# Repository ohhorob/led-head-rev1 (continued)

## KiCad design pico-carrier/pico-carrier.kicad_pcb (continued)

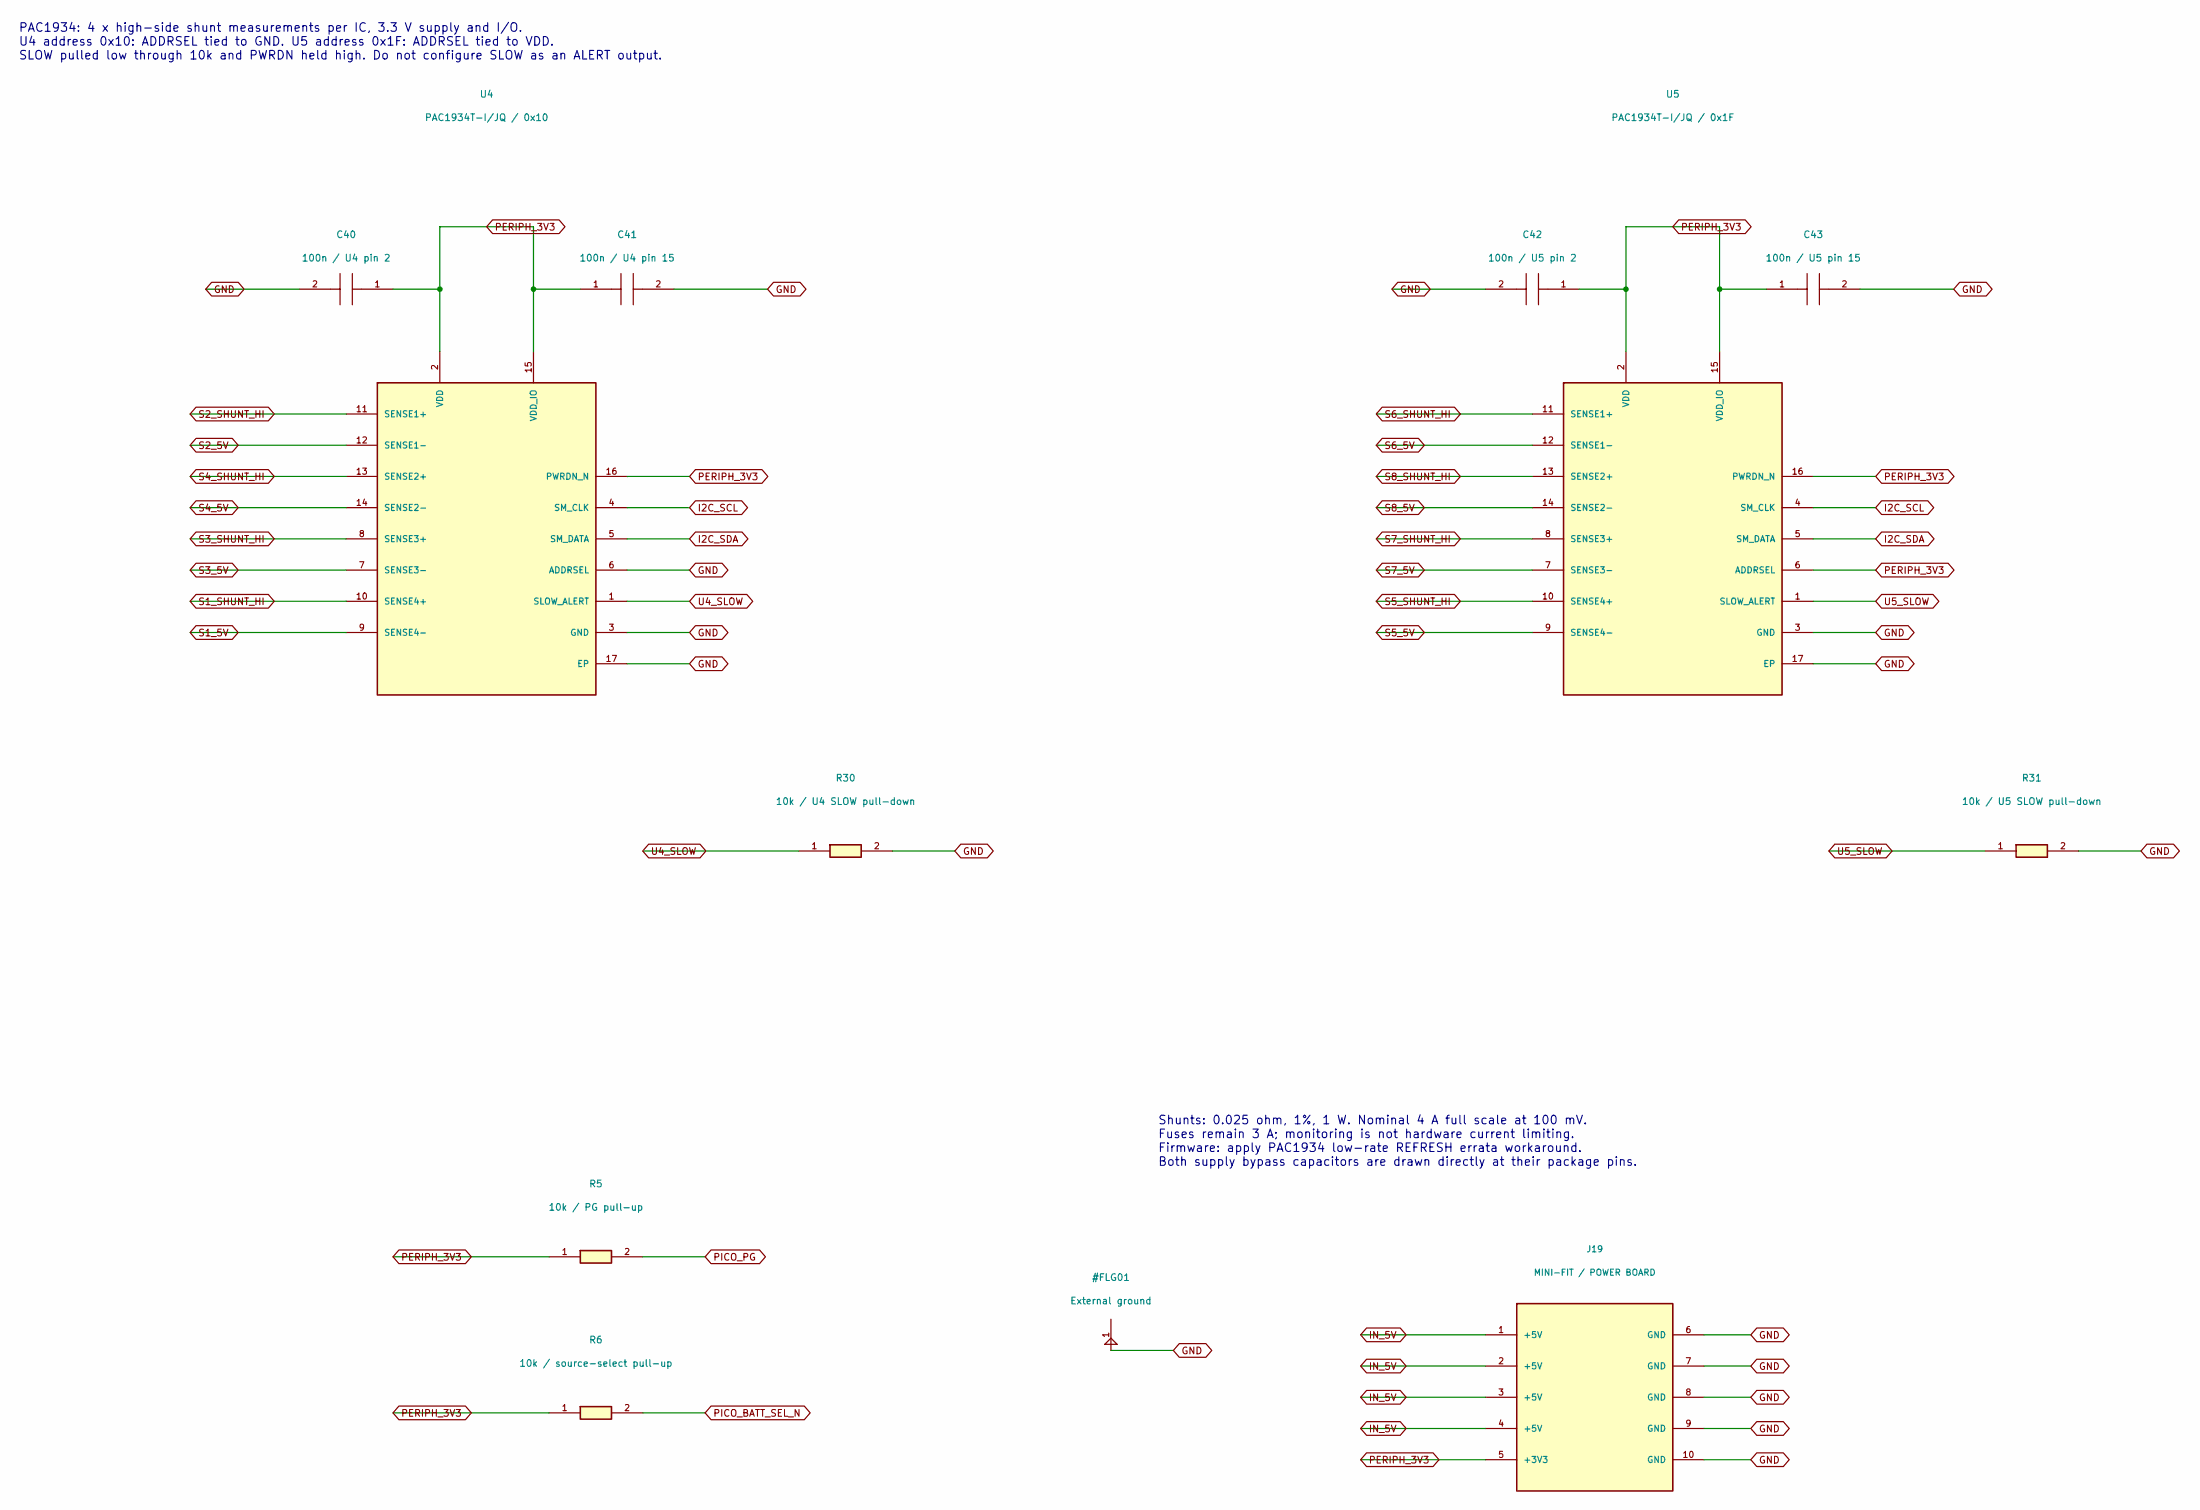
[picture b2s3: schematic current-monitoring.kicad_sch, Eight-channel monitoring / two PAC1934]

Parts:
C40: 100n / U4 pin 2; C_0805_2012Metric
C41: 100n / U4 pin 15; C_0805_2012Metric
C42: 100n / U5 pin 2; C_0805_2012Metric
C43: 100n / U5 pin 15; C_0805_2012Metric
J19: MINI-FIT / POWER BOARD; Molex_Mini-Fit_Jr_5566-10A_2x05_P4.20mm_Vertical; MPN 0039281103
R5: 10k / PG pull-up; R_0805_2012Metric
R6: 10k / source-select pull-up; R_0805_2012Metric
R30: 10k / U4 SLOW pull-down; R_0805_2012Metric
R31: 10k / U5 SLOW pull-down; R_0805_2012Metric
U4: PAC1934T-I/JQ / 0x10; UQFN-16-1EP_4x4mm_P0.65mm_EP2.7x2.7mm; MPN PAC1934T-I/JQ
U5: PAC1934T-I/JQ / 0x1F; UQFN-16-1EP_4x4mm_P0.65mm_EP2.7x2.7mm; MPN PAC1934T-I/JQ

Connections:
GND: C40.2, C41.2, C42.2, C43.2, J19.6 (GND), J19.7 (GND), J19.8 (GND), J19.9 (GND), J19.10 (GND), R30.2, R31.2, U4.3 (GND), U4.6 (ADDRSEL), U4.17 (EP), U5.3 (GND), U5.17 (EP); also elsewhere on the board
I2C_SCL: U4.4 (SM_CLK), U5.4 (SM_CLK); also elsewhere on the board
I2C_SDA: U4.5 (SM_DATA), U5.5 (SM_DATA); also elsewhere on the board
IN_5V: J19.1 (+5V), J19.2 (+5V), J19.3 (+5V), J19.4 (+5V); also elsewhere on the board
PERIPH_3V3: C40.1, C41.1, C42.1, C43.1, J19.5 (+3V3), R5.1, R6.1, U4.2 (VDD), U4.15 (VDD_IO), U4.16 (PWRDN_N), U5.2 (VDD), U5.6 (ADDRSEL), U5.15 (VDD_IO), U5.16 (PWRDN_N); also elsewhere on the board
PICO_BATT_SEL_N: R6.2; also elsewhere on the board
PICO_PG: R5.2; also elsewhere on the board
S1_5V: U4.9 (SENSE4-); also elsewhere on the board
S1_SHUNT_HI: U4.10 (SENSE4+); also elsewhere on the board
S2_5V: U4.12 (SENSE1-); also elsewhere on the board
S2_SHUNT_HI: U4.11 (SENSE1+); also elsewhere on the board
S3_5V: U4.7 (SENSE3-); also elsewhere on the board
S3_SHUNT_HI: U4.8 (SENSE3+); also elsewhere on the board
S4_5V: U4.14 (SENSE2-); also elsewhere on the board
S4_SHUNT_HI: U4.13 (SENSE2+); also elsewhere on the board
S5_5V: U5.9 (SENSE4-); also elsewhere on the board
S5_SHUNT_HI: U5.10 (SENSE4+); also elsewhere on the board
S6_5V: U5.12 (SENSE1-); also elsewhere on the board
S6_SHUNT_HI: U5.11 (SENSE1+); also elsewhere on the board
S7_5V: U5.7 (SENSE3-); also elsewhere on the board
S7_SHUNT_HI: U5.8 (SENSE3+); also elsewhere on the board
S8_5V: U5.14 (SENSE2-); also elsewhere on the board
S8_SHUNT_HI: U5.13 (SENSE2+); also elsewhere on the board
U4_SLOW: R30.1, U4.1 (SLOW_ALERT)
U5_SLOW: R31.1, U5.1 (SLOW_ALERT)

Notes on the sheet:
PAC1934: 4 x high-side shunt measurements per IC, 3.3 V supply and I/O. U4 address 0x10: ADDRSEL tied to GND. U5 address 0x1F: ADDRSEL tied to VDD. SLOW pulled low through 10k and PWRDN held high. Do not configure SLOW as an ALERT output.
Shunts: 0.025 ohm, 1%, 1 W. Nominal 4 A full scale at 100 mV. Fuses remain 3 A; monitoring is not hardware current limiting. Firmware: apply PAC1934 low-rate REFRESH errata workaround. Both supply bypass capacitors are drawn directly at their package pins.

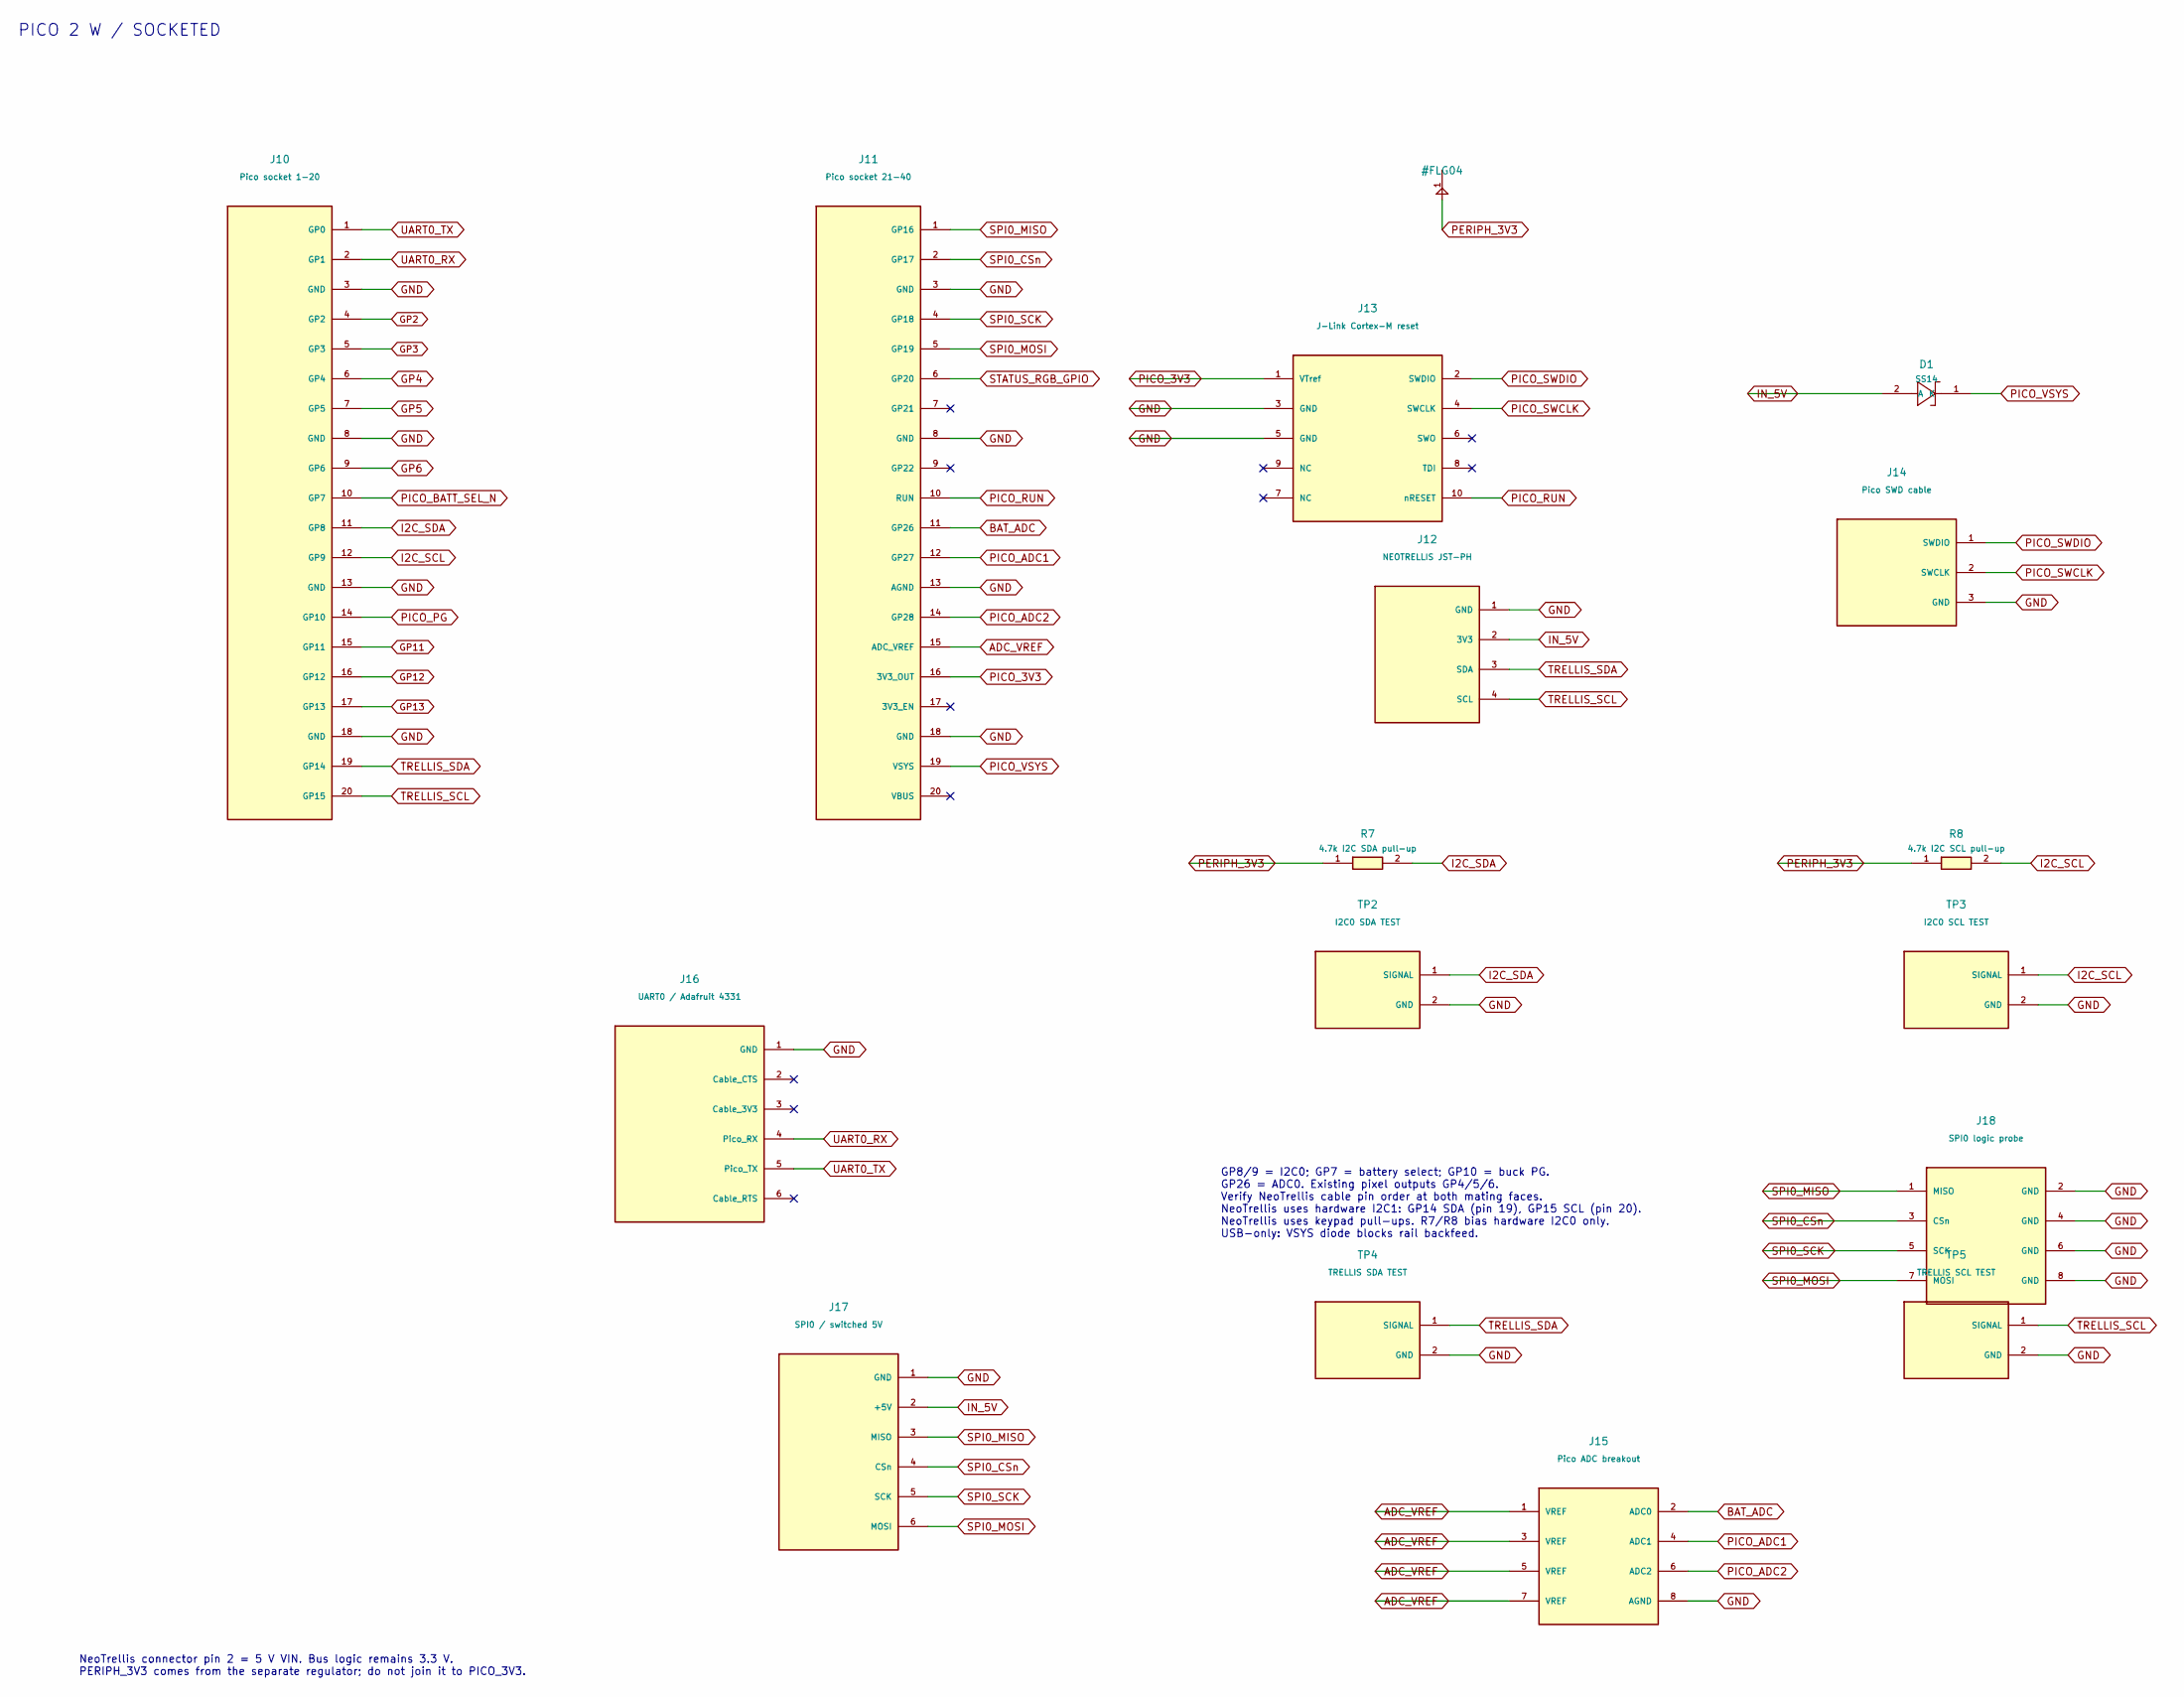
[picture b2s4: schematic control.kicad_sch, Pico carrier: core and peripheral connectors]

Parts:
D1: SS14; D_SMA
J10: Pico socket 1-20; PinSocket_1x20_P2.54mm_Vertical
J11: Pico socket 21-40; PinSocket_1x20_P2.54mm_Vertical
J12: NEOTRELLIS JST-PH; JST_PH_B4B-PH-K_1x04_P2.00mm_Vertical
J13: J-Link Cortex-M reset; Samtec_FTSH-105-01-L-DV_2x05_P1.27mm_SMT
J14: Pico SWD cable; PinHeader_1x03_P2.54mm_Vertical
J15: Pico ADC breakout; PinHeader_2x04_P2.54mm_Vertical
J16: UART0 / Adafruit 4331; PinHeader_1x06_P2.54mm_Vertical
J17: SPI0 / switched 5V; JST_PH_B6B-PH-K_1x06_P2.00mm_Vertical
J18: SPI0 logic probe; PinHeader_2x04_P2.54mm_Vertical
R7: 4.7k I2C SDA pull-up; R_0805_2012Metric
R8: 4.7k I2C SCL pull-up; R_0805_2012Metric
TP2: I2C0 SDA TEST; PinHeader_1x02_P2.54mm_Vertical
TP3: I2C0 SCL TEST; PinHeader_1x02_P2.54mm_Vertical
TP4: TRELLIS SDA TEST; PinHeader_1x02_P2.54mm_Vertical
TP5: TRELLIS SCL TEST; PinHeader_1x02_P2.54mm_Vertical

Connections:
ADC_VREF: J11.15 (ADC_VREF), J15.1 (VREF), J15.3 (VREF), J15.5 (VREF), J15.7 (VREF)
BAT_ADC: J11.11 (GP26), J15.2 (ADC0); also elsewhere on the board
GND: J10.3 (GND), J10.8 (GND), J10.13 (GND), J10.18 (GND), J11.3 (GND), J11.8 (GND), J11.13 (AGND), J11.18 (GND), J12.1 (GND), J13.3 (GND), J13.5 (GND), J14.3 (GND), J15.8 (AGND), J16.1 (GND), J17.1 (GND), J18.2 (GND), J18.4 (GND), J18.6 (GND), J18.8 (GND), TP2.2 (GND), TP3.2 (GND), TP4.2 (GND), TP5.2 (GND); also elsewhere on the board
GP2: J10.4 (GP2); also elsewhere on the board
GP3: J10.5 (GP3); also elsewhere on the board
GP4: J10.6 (GP4); also elsewhere on the board
GP5: J10.7 (GP5); also elsewhere on the board
GP6: J10.9 (GP6); also elsewhere on the board
GP11: J10.15 (GP11); also elsewhere on the board
GP12: J10.16 (GP12); also elsewhere on the board
GP13: J10.17 (GP13); also elsewhere on the board
I2C_SCL: J10.12 (GP9), R8.2, TP3.1 (SIGNAL); also elsewhere on the board
I2C_SDA: J10.11 (GP8), R7.2, TP2.1 (SIGNAL); also elsewhere on the board
IN_5V: D1.2 (A), J12.2 (3V3), J17.2 (+5V); also elsewhere on the board
PERIPH_3V3: R7.1, R8.1; also elsewhere on the board
PICO_3V3: J11.16 (3V3_OUT), J13.1 (VTref); also elsewhere on the board
PICO_ADC1: J11.12 (GP27), J15.4 (ADC1)
PICO_ADC2: J11.14 (GP28), J15.6 (ADC2)
PICO_BATT_SEL_N: J10.10 (GP7); also elsewhere on the board
PICO_PG: J10.14 (GP10); also elsewhere on the board
PICO_RUN: J11.10 (RUN), J13.10 (nRESET)
PICO_SWCLK: J13.4 (SWCLK), J14.2 (SWCLK)
PICO_SWDIO: J13.2 (SWDIO), J14.1 (SWDIO)
PICO_VSYS: D1.1 (K), J11.19 (VSYS)
SPI0_CSn: J11.2 (GP17), J17.4 (CSn), J18.3 (CSn)
SPI0_MISO: J11.1 (GP16), J17.3 (MISO), J18.1 (MISO)
SPI0_MOSI: J11.5 (GP19), J17.6 (MOSI), J18.7 (MOSI)
SPI0_SCK: J11.4 (GP18), J17.5 (SCK), J18.5 (SCK)
STATUS_RGB_GPIO: J11.6 (GP20); also elsewhere on the board
TRELLIS_SCL: J10.20 (GP15), J12.4 (SCL), TP5.1 (SIGNAL)
TRELLIS_SDA: J10.19 (GP14), J12.3 (SDA), TP4.1 (SIGNAL)
UART0_RX: J10.2 (GP1), J16.4 (Pico_RX)
UART0_TX: J10.1 (GP0), J16.5 (Pico_TX)

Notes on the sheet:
PICO 2 W / SOCKETED
GP8/9 = I2C0; GP7 = battery select; GP10 = buck PG. GP26 = ADC0. Existing pixel outputs GP4/5/6. Verify NeoTrellis cable pin order at both mating faces. NeoTrellis uses hardware I2C1: GP14 SDA (pin 19), GP15 SCL (pin 20). NeoTrellis uses keypad pull-ups. R7/R8 bias hardware I2C0 only. USB-only: VSY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
NeoTrellis connector pin 2 = 5 V VIN. Bus logic remains 3.3 V. PERIPH_3V3 comes from the separate regulator; do not join it to PICO_3V3.

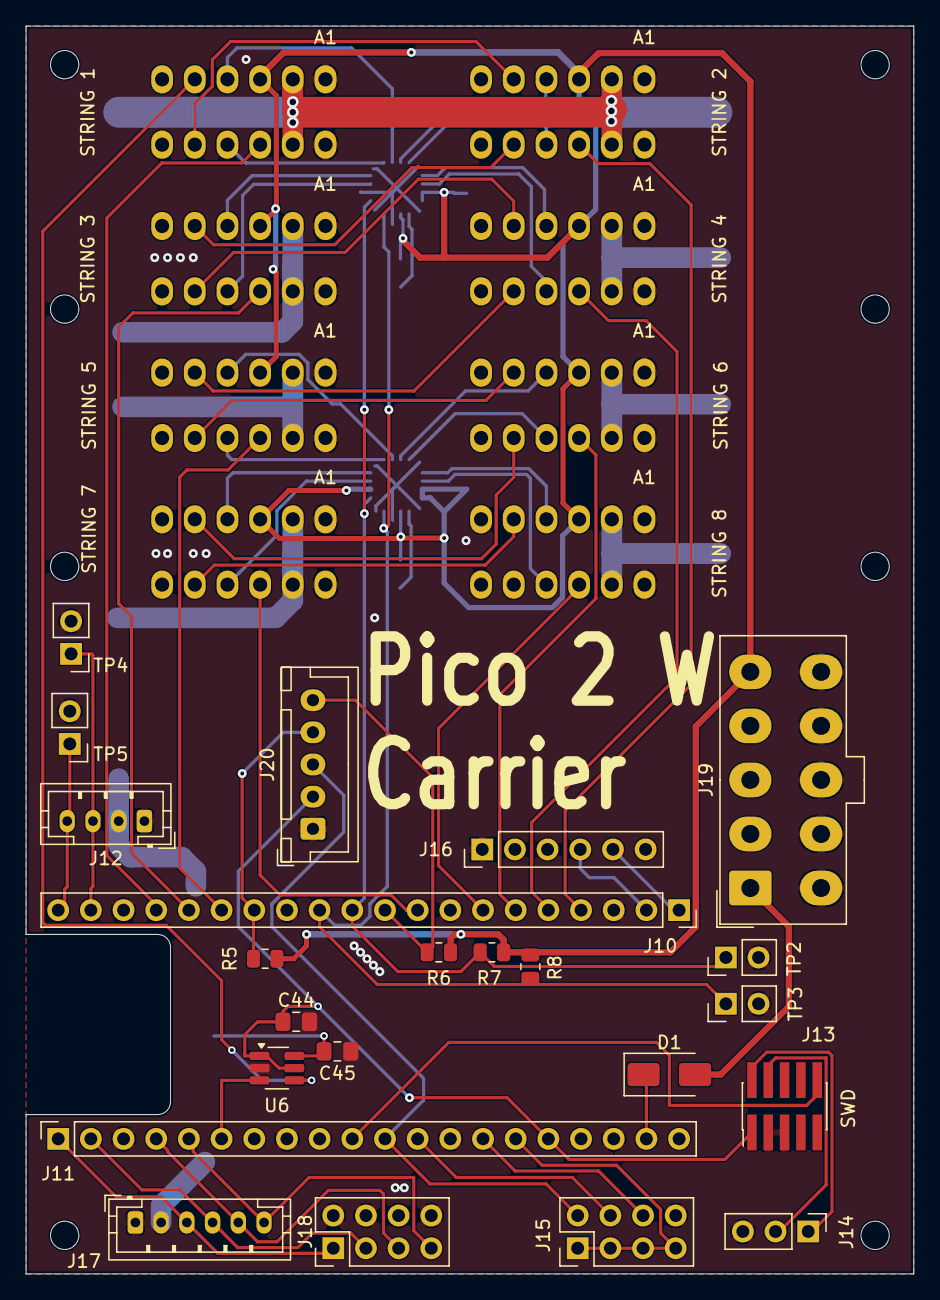
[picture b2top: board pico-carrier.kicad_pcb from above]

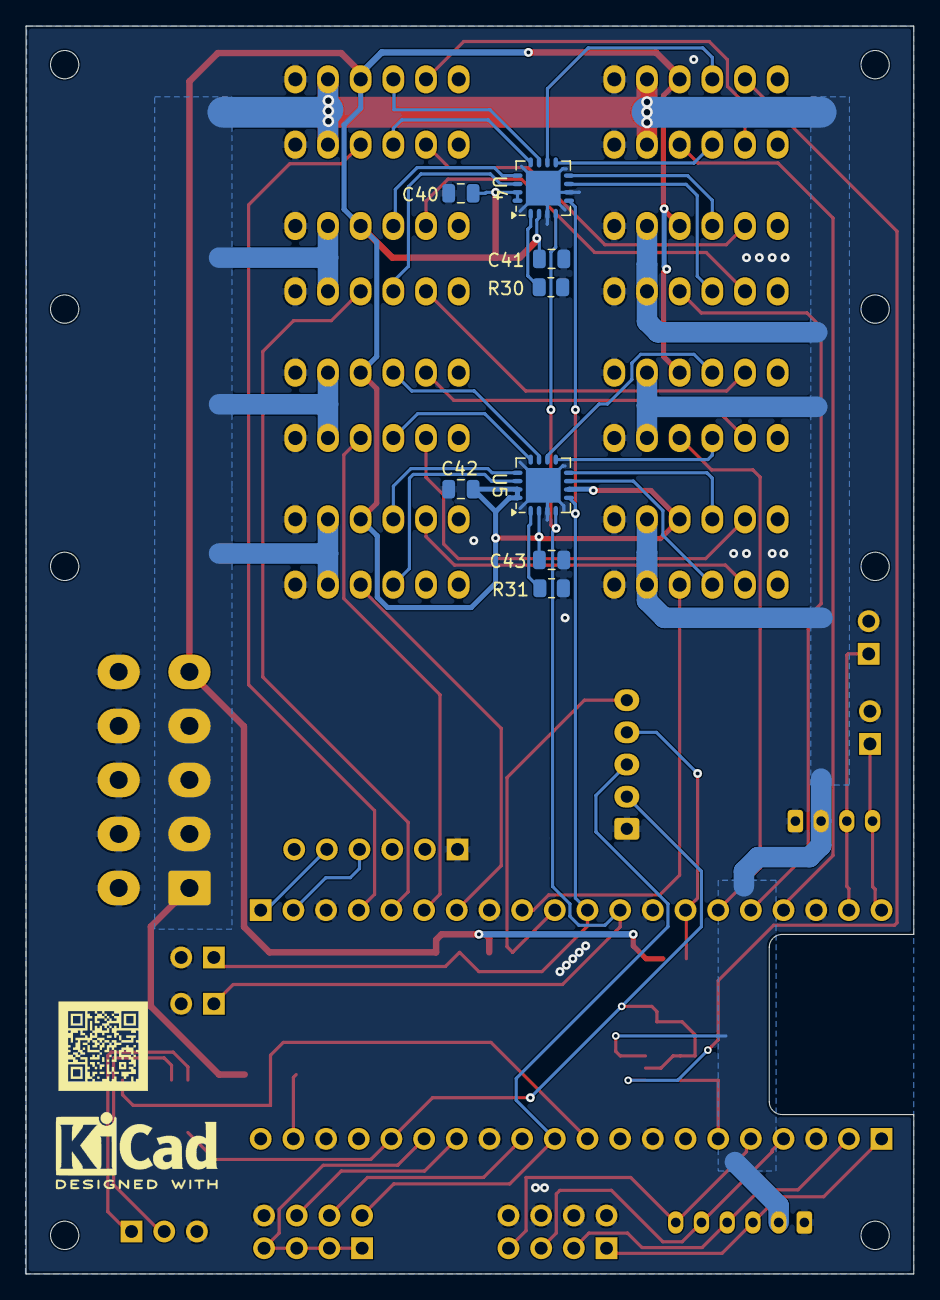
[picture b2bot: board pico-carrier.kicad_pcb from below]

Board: 2 copper layers, 69.0 x 97.0 mm, 47 parts (8 on the bottom side), 59 nets.

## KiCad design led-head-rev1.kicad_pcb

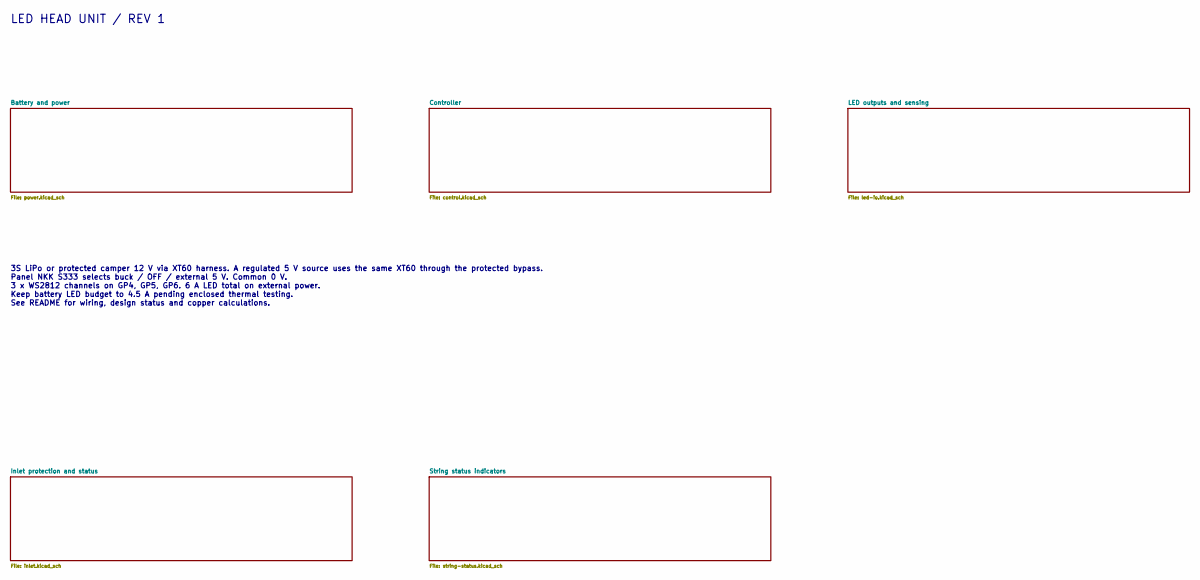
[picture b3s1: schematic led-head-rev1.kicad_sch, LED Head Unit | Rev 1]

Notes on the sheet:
LED HEAD UNIT / REV 1
3S LiPo or protected camper 12 V via XT60 harness. A regulated 5 V source uses the same XT60 through the protected bypass. Panel NKK S333 selects buck / OFF / external 5 V. Common 0 V. 3 x WS2812 channels on GP4, GP5, GP6. 6 A LED total on external power. Keep battery LED budget to 4.5 A pending en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

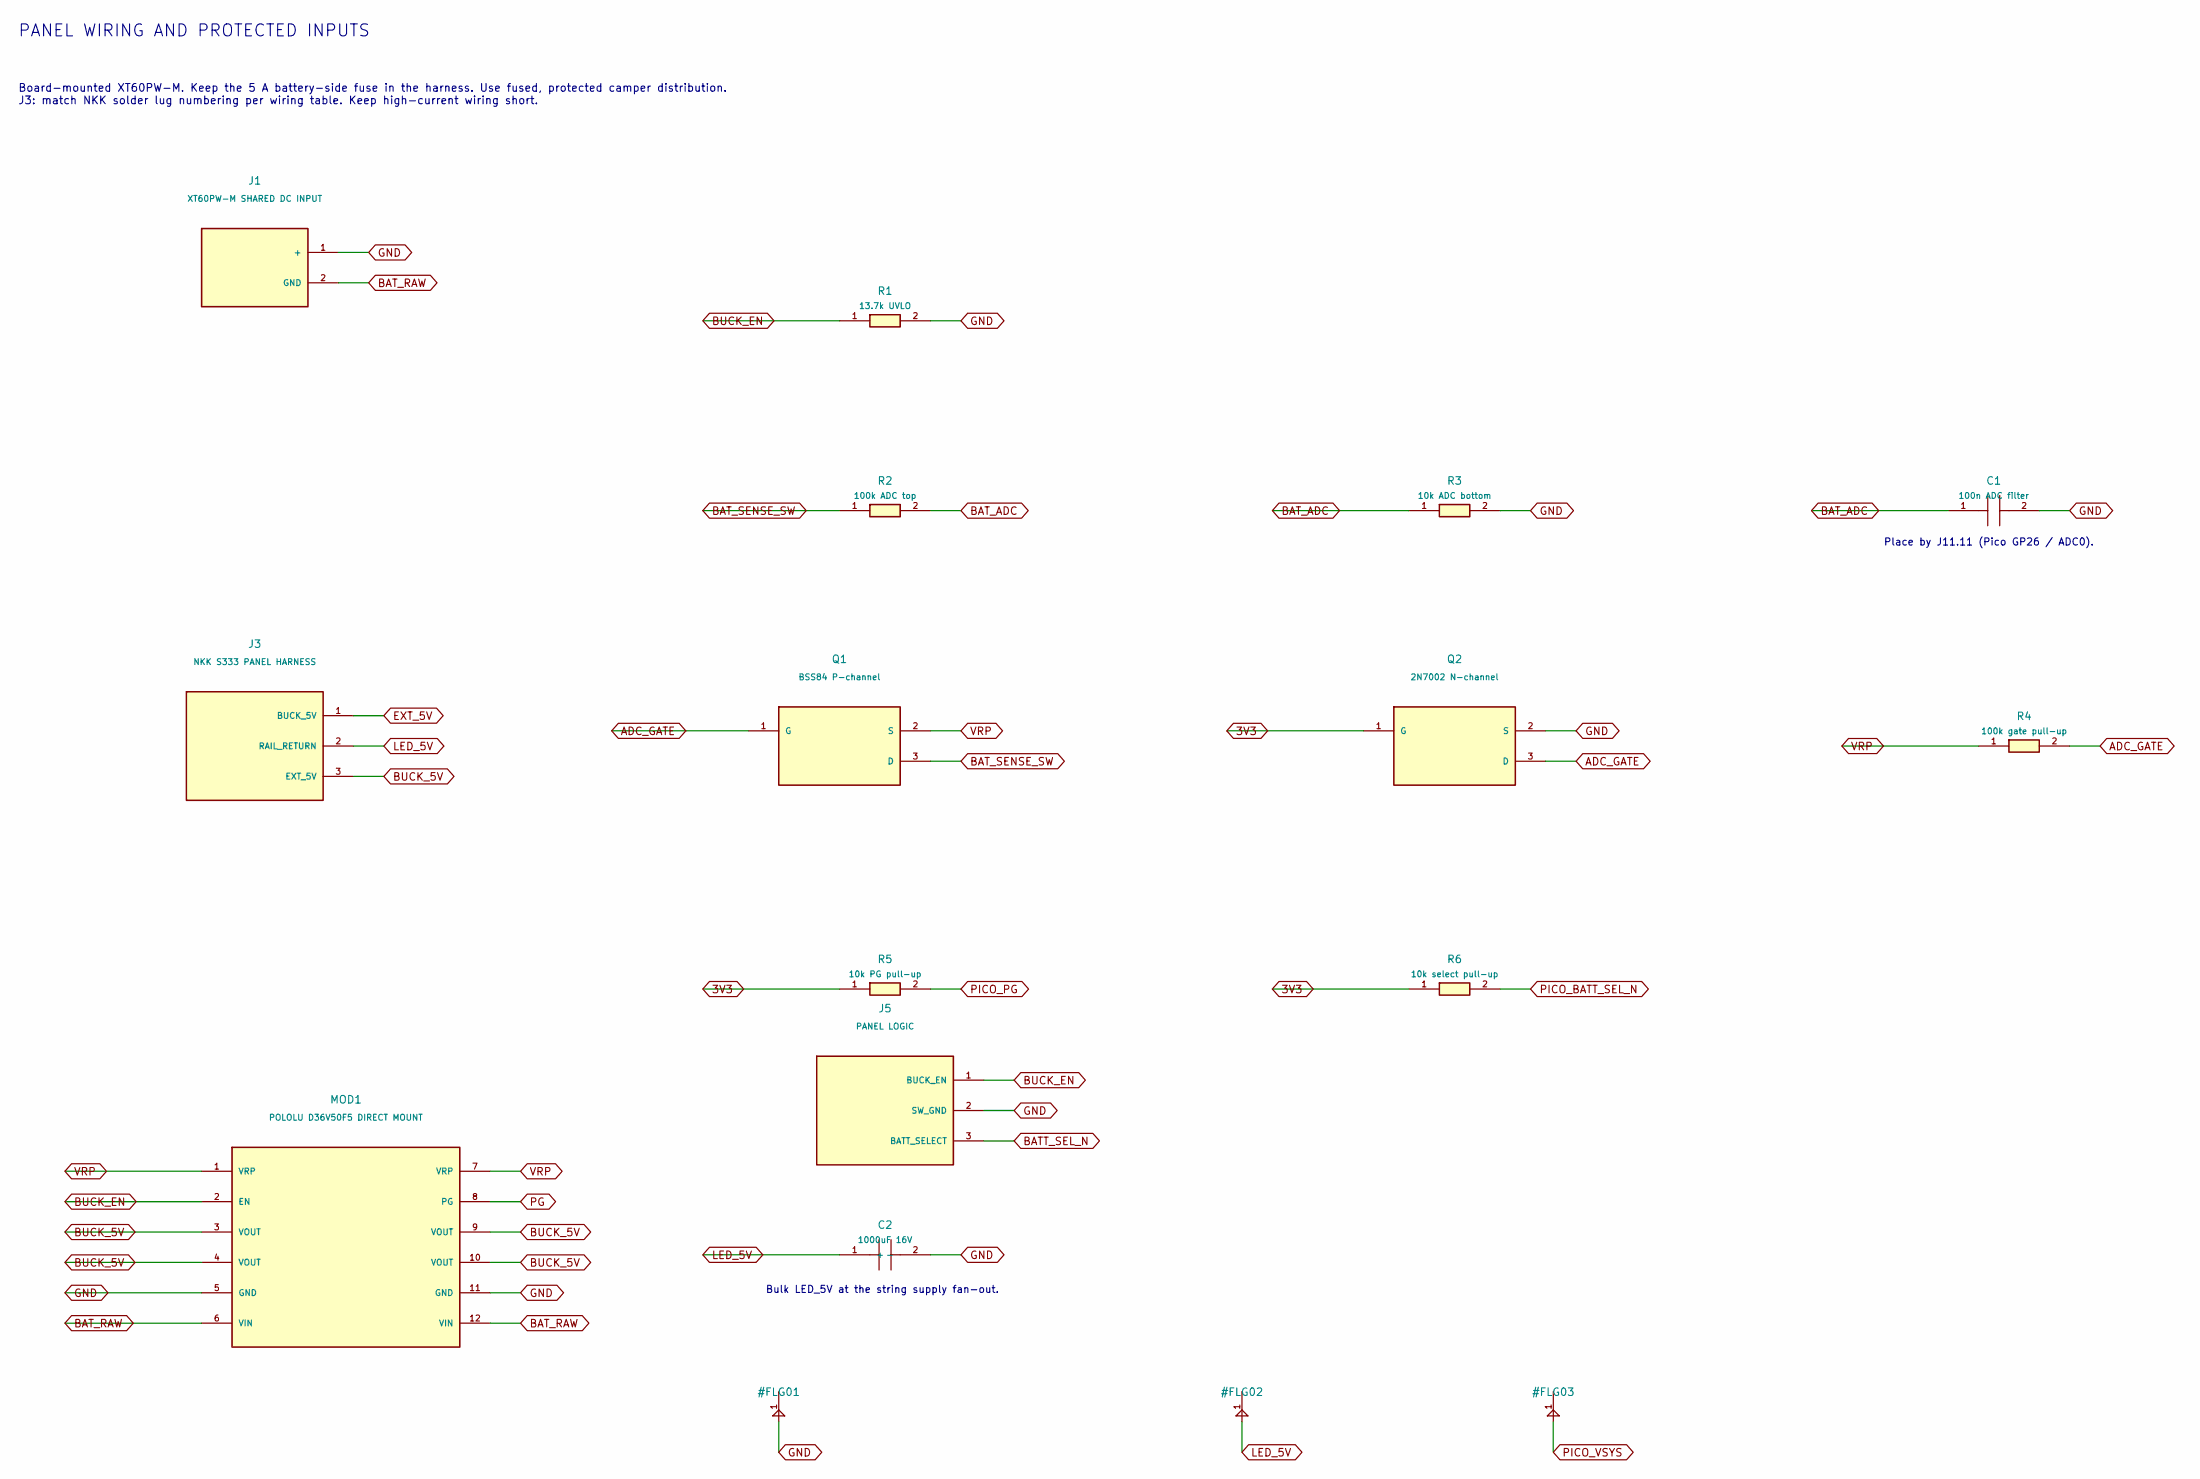
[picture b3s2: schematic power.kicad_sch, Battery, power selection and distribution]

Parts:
C1: 100n ADC filter; C_0805_2012Metric
C2: 1000uF 16V; CP_Radial_D10.0mm_P5.00mm
J1: XT60PW-M SHARED DC INPUT; AMASS_XT60PW-M_1x02_P7.20mm_Horizontal
J3: NKK S333 PANEL HARNESS; TerminalBlock_Phoenix_MKDS-1,5-3-5.08_1x03_P5.08mm_Horizont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
J5: PANEL LOGIC; JST_XH_B3B-XH-A_1x03_P2.50mm_Vertical
MOD1: POLOLU D36V50F5 DIRECT MOUNT; Pololu_D36V50Fx_Direct
Q1: BSS84 P-channel; SOT-23
Q2: 2N7002 N-channel; SOT-23
R1: 13.7k UVLO; R_0805_2012Metric
R2: 100k ADC top; R_0805_2012Metric
R3: 10k ADC bottom; R_0805_2012Metric
R4: 100k gate pull-up; R_0805_2012Metric
R5: 10k PG pull-up; R_0805_2012Metric
R6: 10k select pull-up; R_0805_2012Metric

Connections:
3V3: Q2.1 (G), R5.1, R6.1; also elsewhere on the board
ADC_GATE: Q1.1 (G), Q2.3 (D), R4.2
BATT_SEL_N: J5.3 (BATT_SELECT); also elsewhere on the board
BAT_ADC: C1.1, R2.2, R3.1; also elsewhere on the board
BAT_RAW: J1.2 (GND), MOD1.6 (VIN), MOD1.12 (VIN); also elsewhere on the board
BAT_SENSE_SW: Q1.3 (D), R2.1
BUCK_5V: J3.3 (EXT_5V), MOD1.3 (VOUT), MOD1.4 (VOUT), MOD1.9 (VOUT), MOD1.10 (VOUT)
BUCK_EN: J5.1 (BUCK_EN), MOD1.2 (EN), R1.1
EXT_5V: J3.1 (BUCK_5V); also elsewhere on the board
GND: C1.2, C2.2 (-), J1.1 (+), J5.2 (SW_GND), MOD1.5 (GND), MOD1.11 (GND), Q2.2 (S), R1.2, R3.2; also elsewhere on the board
LED_5V: C2.1 (+), J3.2 (RAIL_RETURN); also elsewhere on the board
PG: MOD1.8 (PG); also elsewhere on the board
PICO_BATT_SEL_N: R6.2; also elsewhere on the board
PICO_PG: R5.2; also elsewhere on the board
VRP: MOD1.1 (VRP), MOD1.7 (VRP), Q1.2 (S), R4.1

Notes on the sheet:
PANEL WIRING AND PROTECTED INPUTS
Bulk LED_5V at the string supply fan-out.
Place by J11.11 (Pico GP26 / ADC0).
Board-mounted XT60PW-M. Keep the 5 A battery-side fuse in the harness. Use fused, protected camper distribution. J3: match NKK solder lug numbering per wiring table. Keep high-current wiring short.

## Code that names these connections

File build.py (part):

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control.note(15,12,'PICO 2 W / SOCKETED',2)
socket=fp('Connector_PinSocket_2.54mm','PinSocket_1x20_P2.54mm_Vertical')
place(control,'PicoL','J10','Pico socket 1-20',(60,95),{1:'UART0_TX',2:'UART0_RX',3:G,6:'GP4',7:'GP5',8:G,9:'GP6',10:'PICO_BATT_SEL_N',11:'I2C_SDA',12:'I2C_SCL',13:G,14:'PICO_PG',18:G,19:'TRELLIS_SDA',20:'TRELLIS_SCL'},socket,(56,40),'',270)
place(control,'PicoR','J11','Pico socket 21-40',(160,95),{1:'SPI0_MISO',2:'SPI0_CSn',3:G,4:'SPI0_SCK',5:'SPI0_MOSI',6:'STATUS_RGB_GPIO',8:G,10:'PICO_RUN',11:'BAT_ADC',12:'PICO_ADC1',13:G,14:'PICO_ADC2',15:'ADC_VREF',16:V,18:G,19:'PICO_VSYS'},socket,(7.74,57.78),'',90)
block('JLinkCortexM', [(1,'VTref','passive'),(3,'GND','passive'),(5,'GND','passive'),(7,'NC','passive'),(9,'NC','passive')],
      [(2,'SWDIO','passive'),(4,'SWCLK','passive'),(6,'SWO','passive'),(8,'TDI','passive'),(10,'nRESET','passive')],13)
place(control,'JLinkCortexM','J13','J-Link Cortex-M reset',(245,82),{1:V,2:'PICO_SWDIO',3:G,4:'PICO_SWCLK',5:G,10:'PICO_RUN'},
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status.note(25,22,'GP20 drives three status pixels in string order. The controller sets the colors.',1.3)
status.note(25,181,'Place C53–C55 beside the corresponding LED VDD/GND pads.',1.3)
status.note(175,227,'Place C58 where 5 V enters the status LED chain.',1.3)
place(status,'TXU0101','U8','TXU0101DBVR',(100, 58),['3V3', 'GND', 'STATUS_RGB_GPIO', 'STATUS_RGB_1', '3V3', 'LED_5V'],'Package_TO_SOT_SMD:SOT-23-6',(112, 14),'TXU0101DBVR')
place(status,'SK6812B','D7','SK6812-B / String 1',(90, 127),['GND', 'STATUS_RGB_1', 'LED_5V', 'STATUS_RGB_2'],'LED_SMD:LED_OPSCO_SK6812_PLCC4_5.0x5.0mm_P3.1mm',(108, 34),'SK6812-B')
place(status,'C','C53','100n / LED bypass',(90, 162),['LED_5V', 'GND'],'Capacitor_SMD:C_0805_2012Metric',(116, 34),'')
place(status,'SK6812B','D8','SK6812-B / String 2',(216, 127),['GND', 'STATUS_RGB_2', 'LED_5V', 'STATUS_RGB_3'],'LED_SMD:LED_OPSCO_SK6812_PLCC4_5.0x5.0mm_P3.1mm',(108, 45),'SK6812-B')
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
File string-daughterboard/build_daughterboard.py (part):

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 fps[ref]=f
 # Manufacturer part is recorded in schematic value / README.
 return f
edgepins={'A1':'GND','B1':'GND','A2':'IN_5V','B2':'IN_5V','A3':'PERIPH_3V3','B3':'STRING_DATA_IN','A4':'SHUNT_HI','B4':'STRING_5V','A5':'STATUS_DATA_IN','B5':'STATUS_DATA_OUT','A6':None,'B6':None}
part('EdgeCard','J1','PCB fingers: mates EBC06DRAS',(60.96,66.04),edgepins,'StringCard:'+edge,(20,52))
part('Fuse','F1','3A / 0451003.MRL',(147.32,43.18),{'1':'IN_5V','2':'SHUNT_HI'},'Fuse:Fuse_Littelfuse-NANO2-451_453',(14,33),90,'0451003.MRL')
part('R','R1','50m / 1W / WSL2512R0500FEA',(238.76,43.18),{'1':'SHUNT_HI','2':'STRING_5V'},'StringCard:Vishay_WSL2512_50mR',(14,20),90,'WSL2512R0500FEA')
part('StringOut','J2','STRING: GND / DATA / 5V',(302.26,66.04),{'1':'GND','2':'STRING_DATA','3':'STRING_5V'},'StringCard:JST_XH_S3B-XH-A_1x03_P2.50mm_Horizontal',(22.5,6),180,'S3B-XH-A(LF)(SN)')
part('TXU0101','U1','TXU0101DBVR / string',(160.02,114.3),{'1':'PERIPH_3V3','2':'GND','3':'STRING_DATA_IN','4':'STRING_BUF','5':'PERIPH_3V3','6':'STRING_5V'},'Package_TO_SOT_SMD:SOT-23-6',(25,20),0,'TXU0101DBVR')
part('R','R2','220R / string data',(233.68,116.84),{'1':'STRING_BUF','2':'STRING_DATA'},'Resistor_SMD:R_0805_2012Metric',(25,14),0,'RC0805FR-07220RL')
part('C','C1','100n / next to U1 VCCA pin 1',(119.38,149.86),{'1':'PERIPH_3V3','2':'GND'},'Capacitor_SMD:C_0805_2012Metric',(21,23),0)
part('C','C2','100n / next to U1 VCCB pin 6',(210.82,149.86),{'1':'STRING_5V','2':'GND'},'Capacitor_SMD:C_0805_2012Metric',(25,24),0)
part('C','C3','10u / 16V / string output buffering',(330.2,139.7),{'1':'STRING_5V','2':'GND'},'Capacitor_SMD:C_1206_3216Metric',(15,12),0)
part('TXU0101','U2','TXU0101DBVR / status',(160.02,205.74),{'1':'PERIPH_3V3','2':'GND','3':'STATUS_DATA_IN','4':'STATUS_BUF','5':'PERIPH_3V3','6':'IN_5V'},'Package_TO_SOT_SMD:SOT-23-6',(26,33),0,'TXU0101DBVR')
part('StatusRGB','D1','OPSCO SK6812-B-012 / status',(330.2,205.74),{'1':'GND','2':'STATUS_LED_IN','3':'IN_5V','4':'STATUS_DATA_OUT'},'LED_SMD:LED_OPSCO_SK6812_PLCC4_5.0x5.0mm_P3.1mm',(33,17),0,'SK6812-B-012')
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
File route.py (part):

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        track(net, k.F_Cu, .2, prior[2], endpoint)
        add_segment(0, prior[2], endpoint, .2, net)
        ends[index] = (*prior[:2], endpoint, (0,))
    for net, pin, target, level in [('BAT_RAW','5',(84,13),0), ('EXT_5V','6',(87.4,11.5),2)]:
        ends = endpoints[net]
        index = next(j for j, item in enumerate(ends) if item[:2] == ('U5', pin))
        ends[index] = ('U5', pin, target, (level,))
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        for l in range(len(layers)): add_segment(l,end,end,.65,n)
        ends[j]=(*ep[:2],end,(1,2))

    for n,pin in [('S2_SHUNT_HI','1'),('S2_5V','2')]:
        ends=endpoints[n]
        j=next(i for i,p in enumerate(ends) if p[:2]==('R12',pin))
        ep=ends[j]
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        already[f'S{i}_5V']=[{(f'R{10+i}','2'),(f'J{20+i}','3')}]
    # Sense lines land at the shunt itself, not elsewhere in the power tree.
    for i in (2,1,3):
        for net,pin in [(f'S{i}_5V','2'),(f'S{i}_SHUNT_HI','1')]:
            pads=endpoints[net]
            sense=next(p for p in pads if p[0]=='U4')
            shunt=next(p for p in pads if p[:2]==(f'R{10+i}',pin))
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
